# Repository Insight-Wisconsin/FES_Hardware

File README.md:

# FES_Hardware
Insight Wisconsin's FES R&amp;D team KiCad files

# Required Software:
**KiCad:** PCB layout and design software  
https://www.kicad.org/download/ (Select your OS and then the Github download)
 
**Git:** Version control software  
https://git-scm.com/downloads (Select your OS and then download at the top of the page)

(OPTIONAL)  
**WSL:** Linux command line on Windows  
Run powershell as admin and type wsl --install

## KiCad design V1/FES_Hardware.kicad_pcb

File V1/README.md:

# FES_Hardware
Insight Wisconsin's FES R&amp;D team KiCad files

# Required Software:
**KiCad:** PCB layout and design software  
https://www.kicad.org/download/ (Select your OS and then the Github download)
 
**Git:** Version control software  
https://git-scm.com/downloads (Select your OS and then download at the top of the page)

(OPTIONAL)  
**WSL:** Linux command line on Windows  
Run powershell as admin and type wsl --install

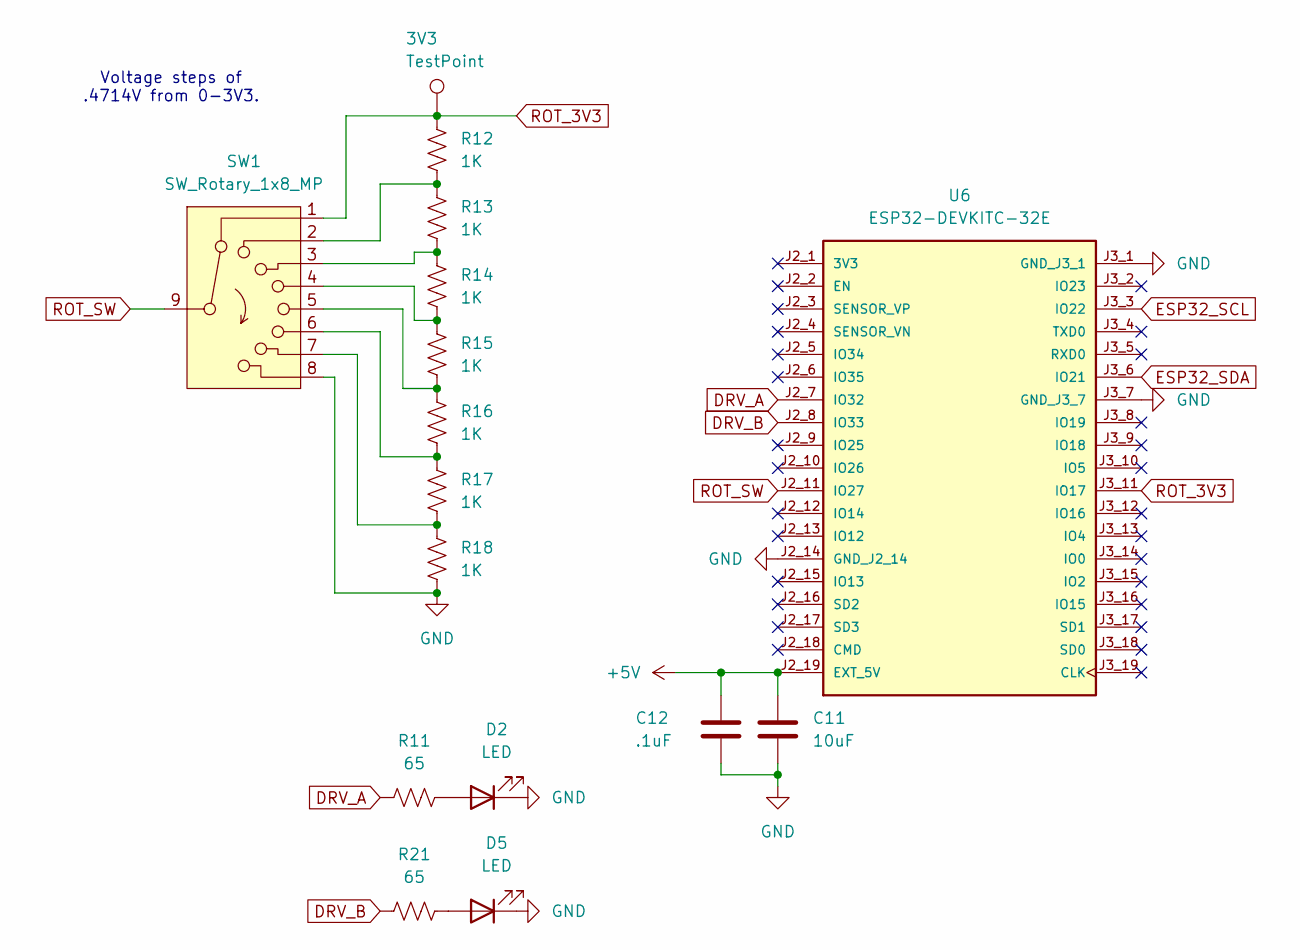
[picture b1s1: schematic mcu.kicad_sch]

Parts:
3V3: TestPoint; TestPoint_Keystone_5019_Minature
C11: 10uF; C_0805_2012Metric_Pad1.18x1.45mm_HandSolder
C12: .1uF; C_0805_2012Metric_Pad1.18x1.45mm_HandSolder
D2, D5: LED; LED_0805_2012Metric_Pad1.15x1.40mm_HandSolder
R11, R21: 65; R_0805_2012Metric_Pad1.20x1.40mm_HandSolder
R12, R13, R14, R15, R16, R17, R18: 1K; R_0805_2012Metric_Pad1.20x1.40mm_HandSolder
SW1: SW_Rotary_1x8_MP; 2925_ADA
U6: ESP32-DEVKITC-32E; MODULE_ESP32-DEVKITC-32E; PARTREV 1.4

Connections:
+5V: C11.1, C12.1, U6.J2_19 (EXT_5V); also elsewhere on the board
DRV_A: R11.1, U6.J2_7 (IO32); also elsewhere on the board
DRV_B: R21.1, U6.J2_8 (IO33); also elsewhere on the board
ESP32_SCL: U6.J3_3 (IO22); also elsewhere on the board
ESP32_SDA: U6.J3_6 (IO21); also elsewhere on the board
GND: C11.2, C12.2, D2.1 (K), D5.1 (K), R18.2, SW1.8, U6.J2_14 (GND_J2_14), U6.J3_1 (GND_J3_1), U6.J3_7 (GND_J3_7); also elsewhere on the board
unnamed: D2.2 (A), R11.2
unnamed: D5.2 (A), R21.2
unnamed: R12.2, R13.1, SW1.2
unnamed: R13.2, R14.1, SW1.3
unnamed: R14.2, R15.1, SW1.4
unnamed: R15.2, R16.1, SW1.5
unnamed: R16.2, R17.1, SW1.6
unnamed: R17.2, R18.1, SW1.7
ROT_3V3: 3V3.1, R12.1, SW1.1, U6.J3_11 (IO17)
ROT_SW: SW1.9, U6.J2_11 (IO27)

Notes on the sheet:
Voltage steps of .4714V from 0-3V3.

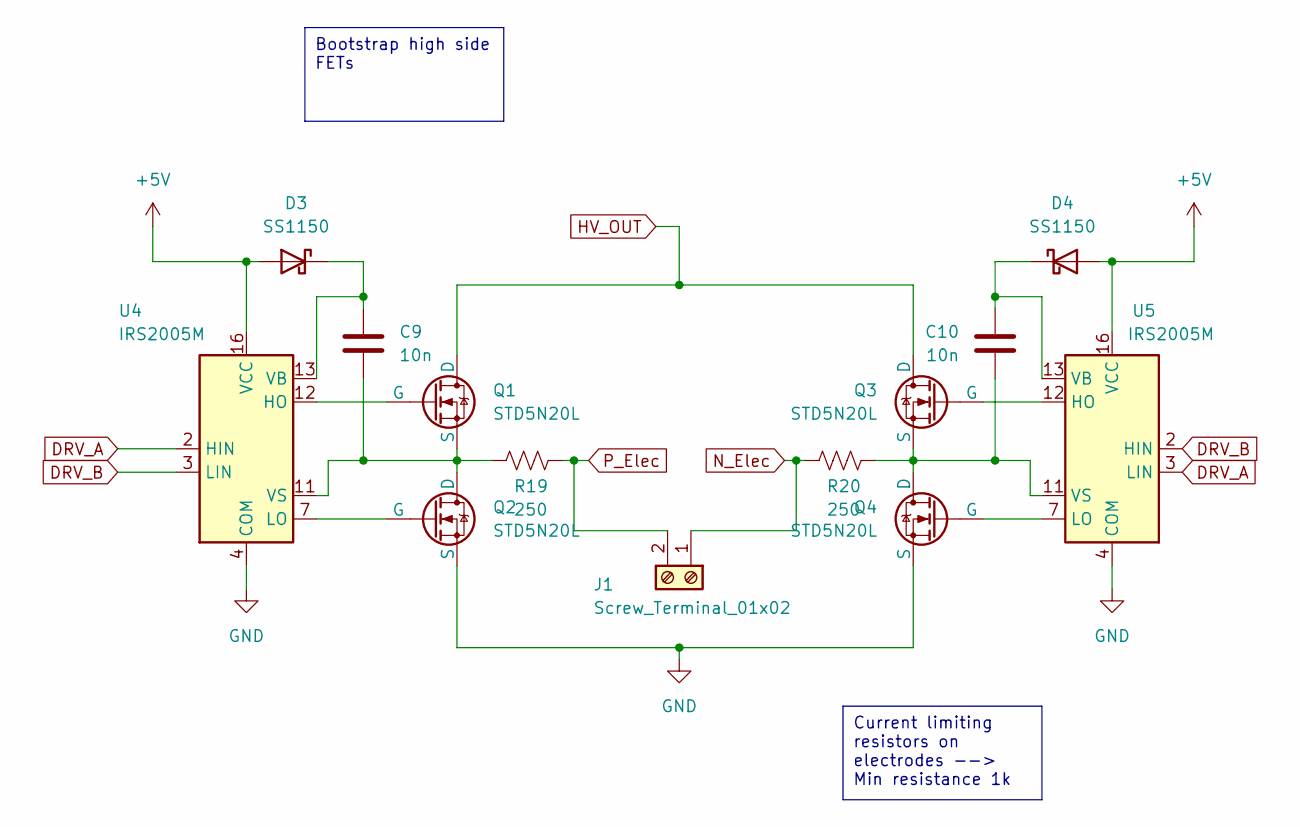
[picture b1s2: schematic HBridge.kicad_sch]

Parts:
C9, C10: 10n; C_0805_2012Metric_Pad1.18x1.45mm_HandSolder
D3, D4: SS1150; D_SMA
J1: Screw_Terminal_01x02; 691137710002
Q1, Q2, Q3, Q4: STD5N20L; STD5N
R19, R20: 250; R_0805_2012Metric_Pad1.20x1.40mm_HandSolder
U4, U5: IRS2005M; Infineon_MLPQ-16-14-1EP_4x4mm_P0.5mm

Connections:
+5V: D3.2 (A), D4.2 (A), U4.16 (VCC), U5.16 (VCC); also elsewhere on the board
DRV_A: U4.2 (HIN), U5.3 (LIN); also elsewhere on the board
DRV_B: U4.3 (LIN), U5.2 (HIN); also elsewhere on the board
GND: Q2.3 (S), Q4.3 (S), U4.4 (COM), U4.17 (COM), U5.4 (COM), U5.17 (COM); also elsewhere on the board
HV_OUT: Q1.1 (D), Q3.1 (D); also elsewhere on the board
N_Elec: J1.1, R20.1
unnamed: C9.1, D3.1 (K), U4.13 (VB)
unnamed: C10.1, D4.1 (K), U5.13 (VB)
unnamed: Q1.2 (G), U4.12 (HO)
unnamed: C9.2, Q1.3 (S), Q2.1 (D), R19.1, U4.11 (VS)
unnamed: Q2.2 (G), U4.7 (LO)
unnamed: Q3.2 (G), U5.12 (HO)
unnamed: C10.2, Q3.3 (S), Q4.1 (D), R20.2, U5.11 (VS)
unnamed: Q4.2 (G), U5.7 (LO)
P_Elec: J1.2, R19.2

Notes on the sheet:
Bootstrap high side FETs
Current limiting resistors on electrodes --> Min resistance 1k

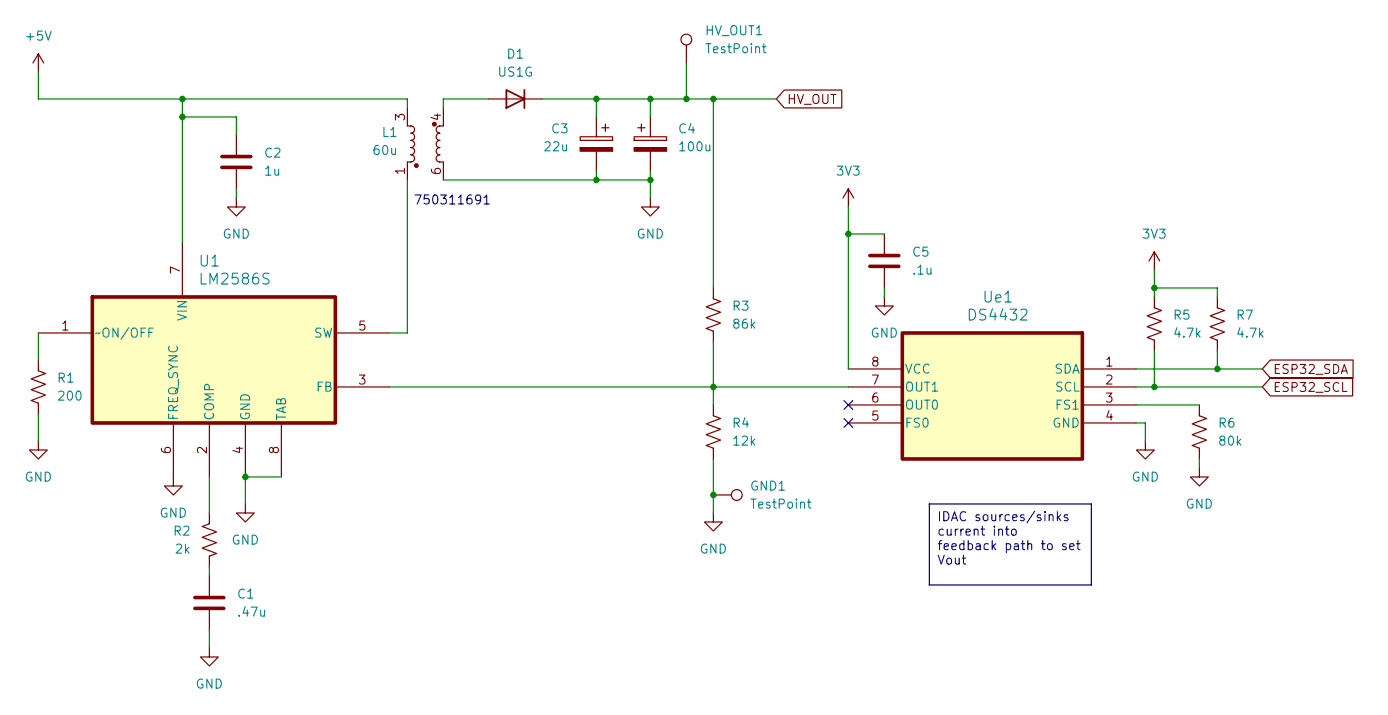
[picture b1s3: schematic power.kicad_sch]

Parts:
C1: .47u; C_0805_2012Metric_Pad1.18x1.45mm_HandSolder
C2: 1u; C_0805_2012Metric_Pad1.18x1.45mm_HandSolder
C3: 22u; C_0805_2012Metric_Pad1.18x1.45mm_HandSolder
C4: 100u; C_0805_2012Metric_Pad1.18x1.45mm_HandSolder
C5: .1u; C_0805_2012Metric_Pad1.18x1.45mm_HandSolder
D1: US1G; D_SMA
GND1: TestPoint; TestPoint_Keystone_5019_Minature
HV_OUT1: TestPoint; TestPoint_Keystone_5019_Minature
L1: 60u; WE 750311691
R1: 200; R_0805_2012Metric_Pad1.20x1.40mm_HandSolder
R2: 2k; R_0805_2012Metric_Pad1.20x1.40mm_HandSolder
R3: 86k; R_0805_2012Metric_Pad1.20x1.40mm_HandSolder
R4: 12k; R_0805_2012Metric_Pad1.20x1.40mm_HandSolder
R5, R7: 4.7k; R_0805_2012Metric_Pad1.20x1.40mm_HandSolder
R6: 80k; R_0805_2012Metric_Pad1.20x1.40mm_HandSolder
U1: LM2586S; TS7B
Ue1: DS4432; 21-0036_U8&plus_1_MXM

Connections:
3V3: C5.1, R5.1, R7.1, Ue1.8 (VCC)
+5V: C2.1, L1.3, U1.7 (VIN); also elsewhere on the board
ESP32_SCL: R5.2, Ue1.2 (SCL); also elsewhere on the board
ESP32_SDA: R7.2, Ue1.1 (SDA); also elsewhere on the board
GND: C1.2, C2.2, C3.2, C4.2, C5.2, GND1.1, L1.6, R1.2, R4.2, R6.2, U1.4 (GND), U1.6 (FREQ_SYNC), U1.8 (TAB), Ue1.4 (GND); also elsewhere on the board
HV_OUT: C3.1, C4.1, D1.1 (K), HV_OUT1.1, R3.1; also elsewhere on the board
unnamed: C1.1, R2.2
unnamed: D1.2 (A), L1.4
unnamed: R2.1, U1.2 (COMP)
unnamed: R3.2, R4.1, U1.3 (FB), Ue1.7 (OUT1)
unnamed: L1.1, U1.5 (SW)
unnamed: R1.1, U1.1 (~ON/OFF)
unnamed: R6.1, Ue1.3 (FS1)

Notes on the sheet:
IDAC sources/sinks current into feedback path to set Vout
750311691

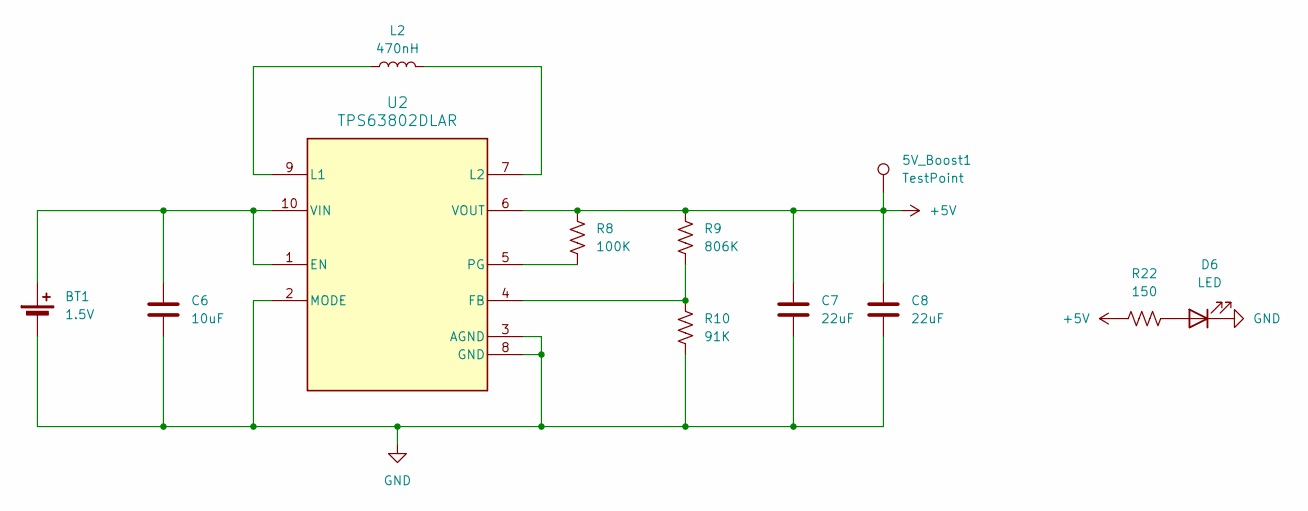
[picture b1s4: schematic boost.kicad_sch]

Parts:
5V_Boost1: TestPoint; TestPoint_Keystone_5019_Minature
BT1: 1.5V; BatteryHolder_Keystone_2460_1xAA
C6: 10uF; C_0805_2012Metric_Pad1.18x1.45mm_HandSolder
C7, C8: 22uF; C_0805_2012Metric_Pad1.18x1.45mm_HandSolder
D6: LED; LED_0805_2012Metric_Pad1.15x1.40mm_HandSolder
L2: 470nH; INDC2016X120N
R8: 100K; R_0805_2012Metric_Pad1.20x1.40mm_HandSolder
R9: 806K; R_0805_2012Metric_Pad1.20x1.40mm_HandSolder
R10: 91K; R_0805_2012Metric_Pad1.20x1.40mm_HandSolder
R22: 150; R_0805_2012Metric_Pad1.20x1.40mm_HandSolder
U2: TPS63802DLAR; DLA0010A

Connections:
+5V: 5V_Boost1.1, C7.1, C8.1, R8.2, R9.2, R22.1, U2.6 (VOUT); also elsewhere on the board
GND: BT1.2 (-), C6.2, C7.2, C8.2, D6.1 (K), R10.1, U2.2 (MODE), U2.3 (AGND), U2.8 (GND); also elsewhere on the board
unnamed: BT1.1 (+), C6.1, U2.1 (EN), U2.10 (VIN)
unnamed: D6.2 (A), R22.2
unnamed: R9.1, R10.2, U2.4 (FB)
unnamed: L2.1, U2.9 (L1)
unnamed: L2.2, U2.7 (L2)
unnamed: R8.1, U2.5 (PG)

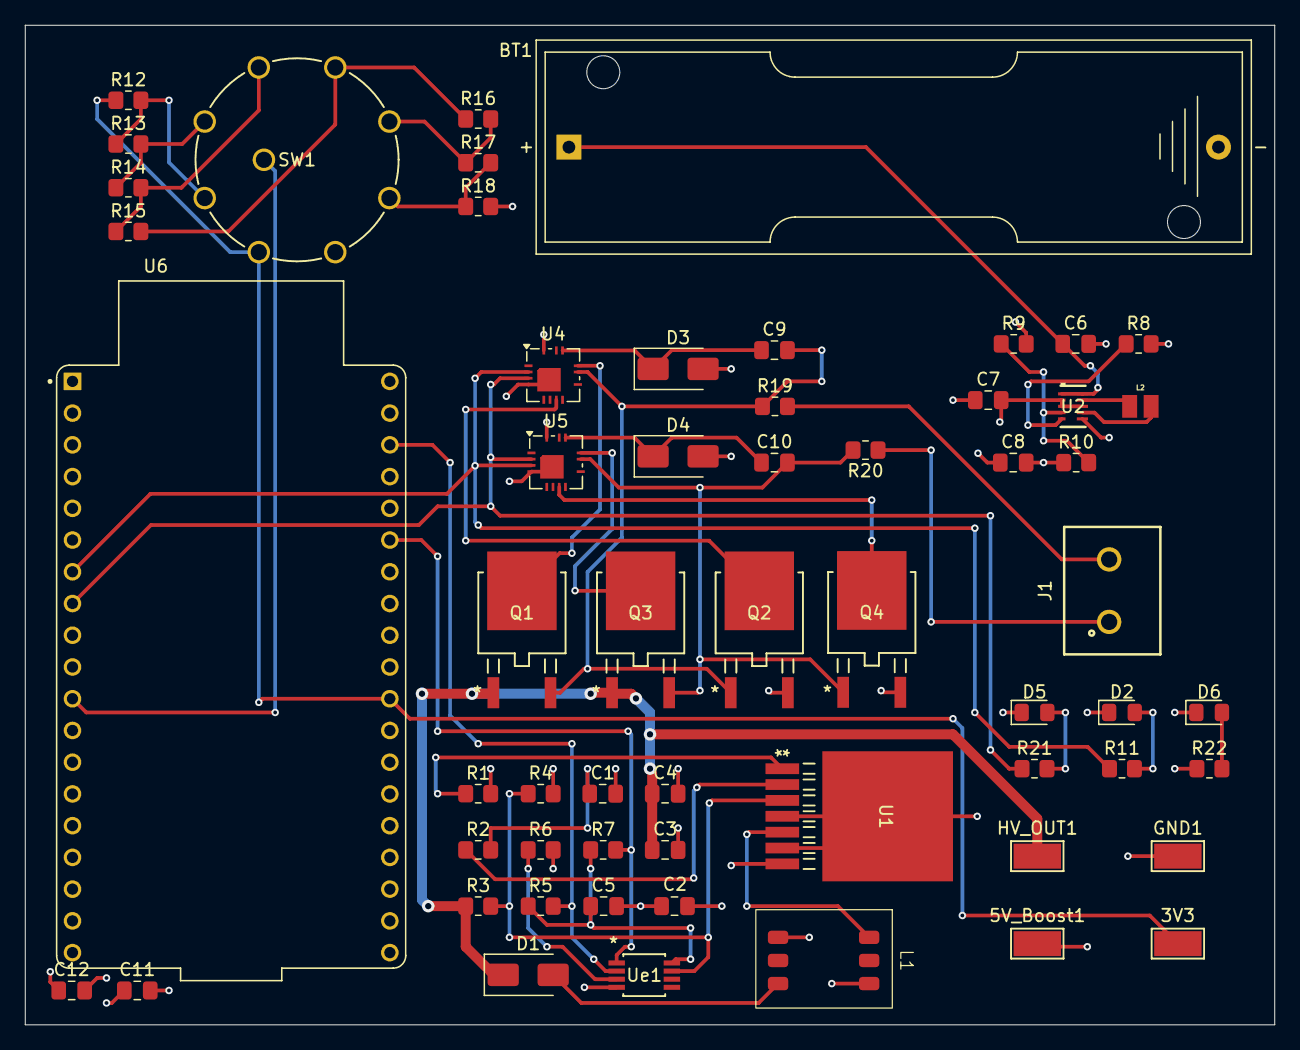
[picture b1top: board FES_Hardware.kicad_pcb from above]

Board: 4 copper layers, 100.0 x 80.0 mm, 59 parts (0 on the bottom side), 41 nets.

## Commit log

2025-03-04 Initialized KiCad Project
2025-03-18 test commit
2025-03-18 remove test
2025-03-19 created individual project sheets
2025-03-19 removed HelloWorld.txt
2025-03-27 Created 1v5 to 3v3 boost schematic for MCU
2025-03-29 Updated boost converter to output 5v instead of 3v3 for ESP32 dev board
2025-03-30 Moved 5v boost to the boost schematic
2025-04-01 Added HV schematic
2025-04-02 Created symbol/footprint for MCU & rotary encoder
2025-04-05 changed transformer, feedback resistors
2025-04-05 Finished rotary switch and updated MCU pinout
2025-04-08 Added H-Bridge, completed HV schematic
2025-04-09 added H-Bridge sheet, symbols, footprints
2025-04-09 updated symbols background to be transparent
2025-04-09 Updated references after merging
2025-04-15 Updated footprints of passive elements to be 0805 Hand-Solder
2025-04-16 added transformer and NMOS footprints
2025-04-16 added footprints
2025-04-16 Hopefully finalized schematic with footprints
2025-04-16 Final schematic design for PCB layout hopefully
2025-04-16 Didn't save, my bad-final schematic
2025-04-16 Started initial KiCad layout
2025-04-17 routed PCB and added status LED for 5V
2025-04-17 second commit for pcb layout
2025-04-17 ryanPCB branch commit for pcb layout
2025-04-17 commiting unsaved changes
2025-04-23 tidied up PCB routing, renamed HV_OUT, changed MCU footprint/schematic
2025-04-29 added decoupling caps to MCU 5V input
2025-09-24 Organized V1 files
2025-09-24 moved README back to home
